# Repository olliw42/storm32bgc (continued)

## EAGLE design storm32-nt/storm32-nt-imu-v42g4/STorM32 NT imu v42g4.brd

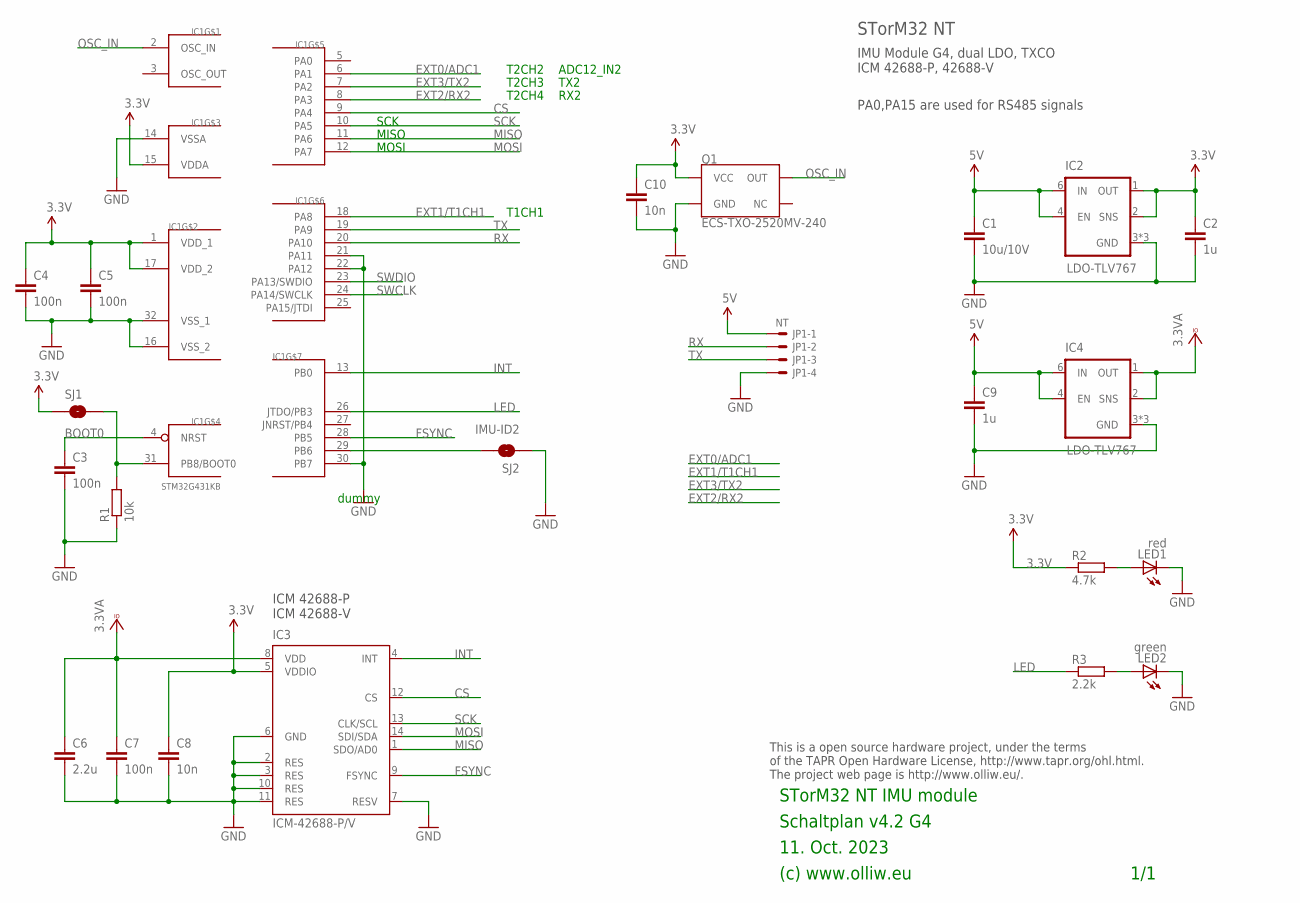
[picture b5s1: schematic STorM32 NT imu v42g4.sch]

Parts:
C1: 10u/10V; C1206
C2: 1u; C0603
C3, C4, C5, C7: 100n; C0402
C6: 2.2u; C0603
C8, C10: 10n; C0402
C9: 1u; C0402
IC1: STM32G431KB; UFQFPN32
IC2, IC4: LDO-TLV767; WSON-6-2X2
IC3: ICM-42688-P/V; LGA14-2.5X3
JP1: NT; SM04B-SRSS-TB
LED1: red; CHIPLED_0603
LED2: green; CHIPLED_0603
Q1: ECS-TXO-2520MV-240; TXCO-25X20
R1: 10k; R0402
R2: 4.7k; R0402
R3: 2.2k; R0402
SJ1: BOOT0; SJ_2S-NO
SJ2: IMU-ID2; SJ_2S-NO

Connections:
3.3V: C2.1, C4.1, C5.1, C8.1, C10.1, IC1.1 (VDD_1), IC1.15 (VDDA), IC1.17 (VDD_2), IC2.1 (OUT), IC2.2 (SNS), IC3.5 (VDDIO), Q1.4 (VCC), R2.1, SJ1.1
3.3VA: C6.1, C7.1, IC3.8 (VDD), IC4.1 (OUT), IC4.2 (SNS)
5V: C1.1, C9.1, IC2.4 (EN), IC2.6 (IN), IC4.4 (EN), IC4.6 (IN), JP1.1
CS: IC1.9 (PA4), IC3.12 (CS)
EXT0/ADC1: IC1.6 (PA1)
EXT1/T1CH1: IC1.18 (PA8)
EXT2/RX2: IC1.8 (PA3)
EXT3/TX2: IC1.7 (PA2)
FSYNC: IC1.28 (PB5), IC3.9 (FSYNC)
GND: C1.2, C2.2, C3.2, C4.2, C5.2, C6.2, C7.2, C8.2, C9.2, C10.2, IC1.14 (VSSA), IC1.16 (VSS_2), IC1.21 (PA11), IC1.22 (PA12), IC1.30 (PB7), IC1.32 (VSS_1), IC2.3 (GND), IC2.5 (GND), IC2.7 (GND), IC3.2 (RES), IC3.3 (RES), IC3.6 (GND), IC3.7 (RESV), IC3.10 (RES), IC3.11 (RES), IC4.3 (GND), IC4.5 (GND), IC4.7 (GND), JP1.4, LED1.C, LED2.C, Q1.2 (GND), R1.1, SJ2.1
INT: IC1.13 (PB0), IC3.4 (INT)
LED: IC1.26 (JTDO/PB3), R3.1
MISO: IC1.11 (PA6), IC3.1 (SDO/AD0)
MOSI: IC1.12 (PA7), IC3.14 (SDI/SDA)
unnamed: C3.1, IC1.4 (NRST)
unnamed: LED2.A, R3.2
unnamed: IC1.31 (PB8/BOOT0), R1.2, SJ1.2
unnamed: IC1.29 (PB6), SJ2.2
unnamed: LED1.A, R2.2
OSC_IN: IC1.2 (OSC_IN), Q1.3 (OUT)
RX: IC1.20 (PA10), JP1.2
SCK: IC1.10 (PA5), IC3.13 (CLK/SCL)
SWCLK: IC1.24 (PA14/SWCLK)
SWDIO: IC1.23 (PA13/SWDIO)
TX: IC1.19 (PA9), JP1.3

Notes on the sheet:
11. Oct. 2023
(c) www.olliw.eu
STorM32 NT IMU module
Schaltplan v4.2 G4
This is a open source hardware project, under the terms of the TAPR Open Hardware License, http://www.tapr.org/ohl.html. The project web page is http://www.olliw.eu/.
1/1
IMU Module G4, dual LDO, TXCO ICM 42688-P, 42688-V
STorM32 NT
SCK
MISO
MOSI
dummy
T2CH3
RX2
TX2
ICM 42688-P ICM 42688-V
T2CH2
ADC12_IN2
T2CH4
T1CH1
PA0,PA15 are used for RS485 signals

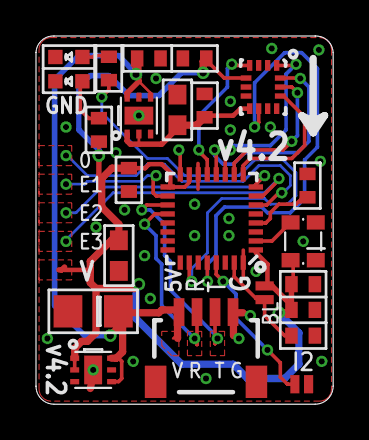
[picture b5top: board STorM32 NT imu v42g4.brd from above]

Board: 2 copper layers, 16.5 x 20.5 mm, 23 parts (0 on the bottom side), 19 nets.

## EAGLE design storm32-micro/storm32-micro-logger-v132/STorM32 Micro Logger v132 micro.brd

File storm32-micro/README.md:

STorM32 Micro Boards
====================

Schemes and designs by OlliW.<br>

The STorM32 Micro boards offered in this folder are published as open source hardware, under the terms of the TAPR Open Hardware License as published by the Free Hardware Foundation, see http://www.tapr.org/ohl.html.

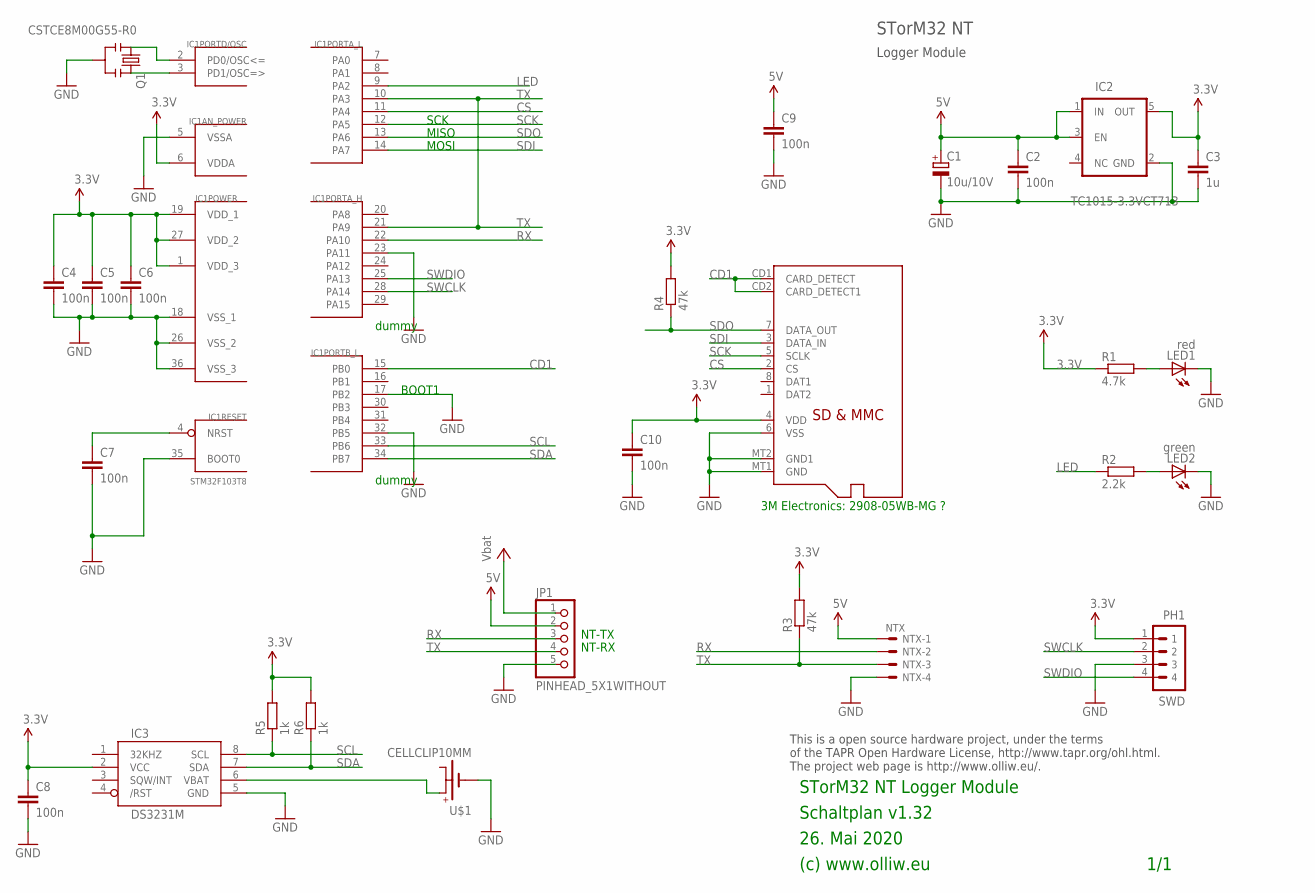
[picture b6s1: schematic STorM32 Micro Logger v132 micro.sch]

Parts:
C1: 10u/10V; SMC_B
C2, C9: 100n; C0603
C3: 1u; C0603
C4, C5, C6, C7, C8, C10: 100n; C0402
IC1: STM32F103T8; VFQFPN36
IC2: TC1015-3.3VCT713; SOT23-5
IC3: DS3231M; SO08
JP1: PINHEAD_5X1WITHOUT; PINHEAD_5X1_WO
LED1: red; CHIPLED_0603
LED2: green; CHIPLED_0603
NTX: NTX; SM04B-SRSS-TB
PH1: SWD; 4X1_1P27_OCT_BILEX
Q1: CSTCE8M00G55-R0; RESONATOR-SMD
R1: 4.7k; R0402
R2: 2.2k; R0402
R3, R4: 47k; R0402
R5, R6: 1k; R0402
U1: 3M 2908-05WB-MG ??; MICROSD
U$1: CELLCLIP10MM; CELLCLIP-10MM

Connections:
3.3V: C3.1, C4.1, C5.1, C6.1, C8.1, C10.1, IC1.1 (VDD_3), IC1.6 (VDDA), IC1.19 (VDD_1), IC1.27 (VDD_2), IC2.5 (OUT), IC3.2 (VCC), PH1.1, R1.1, R3.2, R4.2, R5.2, R6.2, U1.4 (VDD)
5V: C1.+, C2.1, C9.1, IC2.1 (IN), IC2.3 (EN), JP1.2, NTX.1
BAT+: IC3.6 (VBAT), U$1.P$2 (BAT+)
CD1: IC1.15 (PB0), U1.CD1 (CARD_DETECT), U1.CD2 (CARD_DETECT1)
CS: IC1.11 (PA4), U1.2 (CS)
GND: C1.-, C2.2, C3.2, C4.2, C5.2, C6.2, C7.2, C8.2, C9.2, C10.2, IC1.5 (VSSA), IC1.17 (PB2), IC1.18 (VSS_1), IC1.23 (PA11), IC1.26 (VSS_2), IC1.32 (PB5), IC1.35 (BOOT0), IC1.36 (VSS_3), IC2.2 (GND), IC3.5 (GND), JP1.5, LED1.C, LED2.C, NTX.4, PH1.3, Q1.2, U1.6 (VSS), U1.MT1 (GND), U1.MT2 (GND1), U$1.P$1 (GND)
LED: IC1.9 (PA2), R2.1
unnamed: C7.1, IC1.4 (NRST)
unnamed: LED2.A, R2.2
unnamed: IC1.2 (PD0/OSC<=), Q1.1
unnamed: IC1.3 (PD1/OSC=>), Q1.3
unnamed: LED1.A, R1.2
RX: IC1.22 (PA10), JP1.3, NTX.2
SCK: IC1.12 (PA5), U1.5 (SCLK)
SCL: IC1.33 (PB6), IC3.8 (SCL), R5.1
SDA: IC1.34 (PB7), IC3.7 (SDA), R6.1
SDI: IC1.14 (PA7), U1.3 (DATA_IN)
SDO: IC1.13 (PA6), R4.1, U1.7 (DATA_OUT)
SWCLK: IC1.28 (PA14), PH1.2
SWDIO: IC1.25 (PA13), PH1.4
TX: IC1.10 (PA3), IC1.21 (PA9), JP1.4, NTX.3, R3.1
VCC: JP1.1

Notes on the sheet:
26. Mai 2020
(c) www.olliw.eu
STorM32 NT Logger Module
Schaltplan v1.32
This is a open source hardware project, under the terms of the TAPR Open Hardware License, http://www.tapr.org/ohl.html. The project web page is http://www.olliw.eu/.
1/1
Logger Module
STorM32 NT
SCK
MISO
MOSI
BOOT1
dummy
3M Electronics: 2908-05WB-MG ?
NT-RX
NT-TX

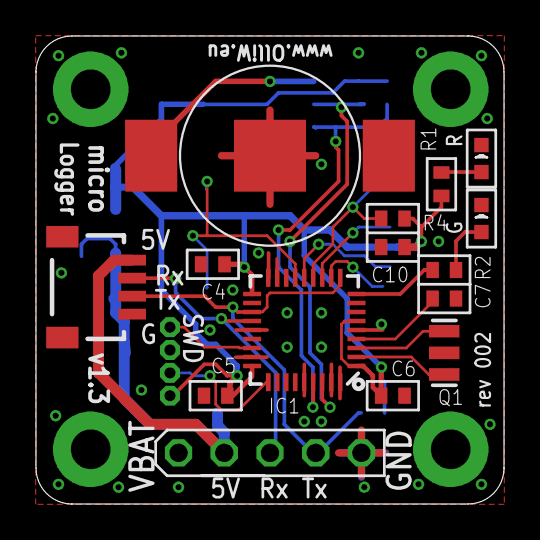
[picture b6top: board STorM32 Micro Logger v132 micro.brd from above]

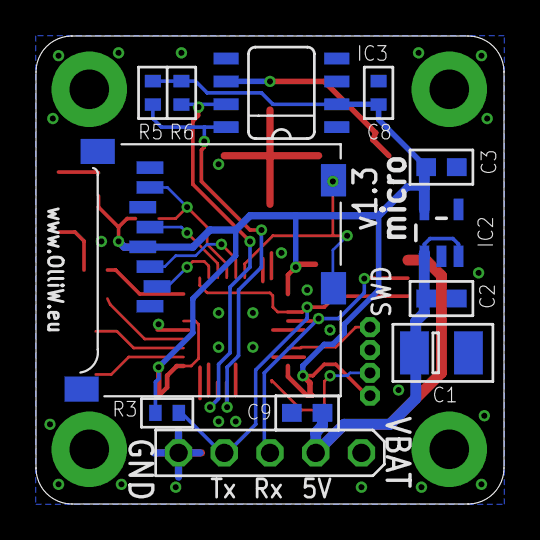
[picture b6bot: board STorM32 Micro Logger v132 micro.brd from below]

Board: 2 copper layers, 26.0 x 26.0 mm, 27 parts (11 on the bottom side), 21 nets.

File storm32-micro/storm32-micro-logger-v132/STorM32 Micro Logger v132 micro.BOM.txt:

Stückliste exportiert aus C:/Users/Olli/Documents/GitHub/storm32bgc/storm32-micro/storm32-micro-logger-v132/STorM32 Micro Logger v132 micro.sch am 05.06.2020 16:31

Part Value              Device                Package            Description                                                 
C1   10u/10V            CPOL-EUSMCB           SMC_B              POLARIZED CAPACITOR, European symbol                        
C2   100n               C-EUC0603             C0603              CAPACITOR, European symbol                                  
C3   1u                 C-EUC0603             C0603              CAPACITOR, European symbol                                  
C4   100n               C-EUC0402             C0402              CAPACITOR, European symbol                                  
C5   100n               C-EUC0402             C0402              CAPACITOR, European symbol                                  
C6   100n               C-EUC0402             C0402              CAPACITOR, European symbol                                  
C7   100n               C-EUC0402             C0402              CAPACITOR, European symbol                                  
C8   100n               C-EUC0402             C0402              CAPACITOR, European symbol                                  
C9   100n               C-EUC0603             C0603              CAPACITOR, European symbol                                  
C10  100n               C-EUC0402             C0402              CAPACITOR, European symbol                                  
IC1  STM32F103T8        STM32F10XTXU6         VFQFPN36           STM32F101/103 36pad VFQPFN36                                
IC2  TC1015-3.3VCT713   V_REG_TPS76433SOT23-5 SOT23-5            Voltage Regulator                                           
IC3  DS3231M            DS3231M               SO08                                                                           
JP1  PINHEAD_5X1WITHOUT PINHEAD_5X1WITHOUT    PINHEAD_5X1_WO                                                                 
LED1 red                LEDCHIPLED_0603       CHIPLED_0603       LED                                                         
LED2 green              LEDCHIPLED_0603       CHIPLED_0603       LED                                                         
NTX  NTX                SM04B-SRSS-TB         SM04B-SRSS-TB      Disconnectable Crimp style connector, 1.0mm pitch4 contacts 
PH1  SWD                P4X1_1P27-OCT_BILEX   4X1_1P27_OCT_BILEX                                                             
Q1   CSTCE8M00G55-R0    RESONATORSMD          RESONATOR-SMD      Resonator                                                   
R1   4.7k               R-EU_R0402            R0402              RESISTOR, European symbol                                   
R2   2.2k               R-EU_R0402            R0402              RESISTOR, European symbol                                   
R3   47k                R-EU_R0402            R0402              RESISTOR, European symbol                                   
R4   47k                R-EU_R0402            R0402              RESISTOR, European symbol                                   
R5   1k                 R-EU_R0402            R0402              RESISTOR, European symbol                                   
R6   1k                 R-EU_R0402            R0402              RESISTOR, European symbol                                   
U$1  CELLCLIP10MM       CELLCLIP10MM          CELLCLIP-10MM                                                                  
U1   3M 2908-05WB-MG ?? MICROSD               MICROSD            Micro-SD / Transflash card holder with SPI pinout

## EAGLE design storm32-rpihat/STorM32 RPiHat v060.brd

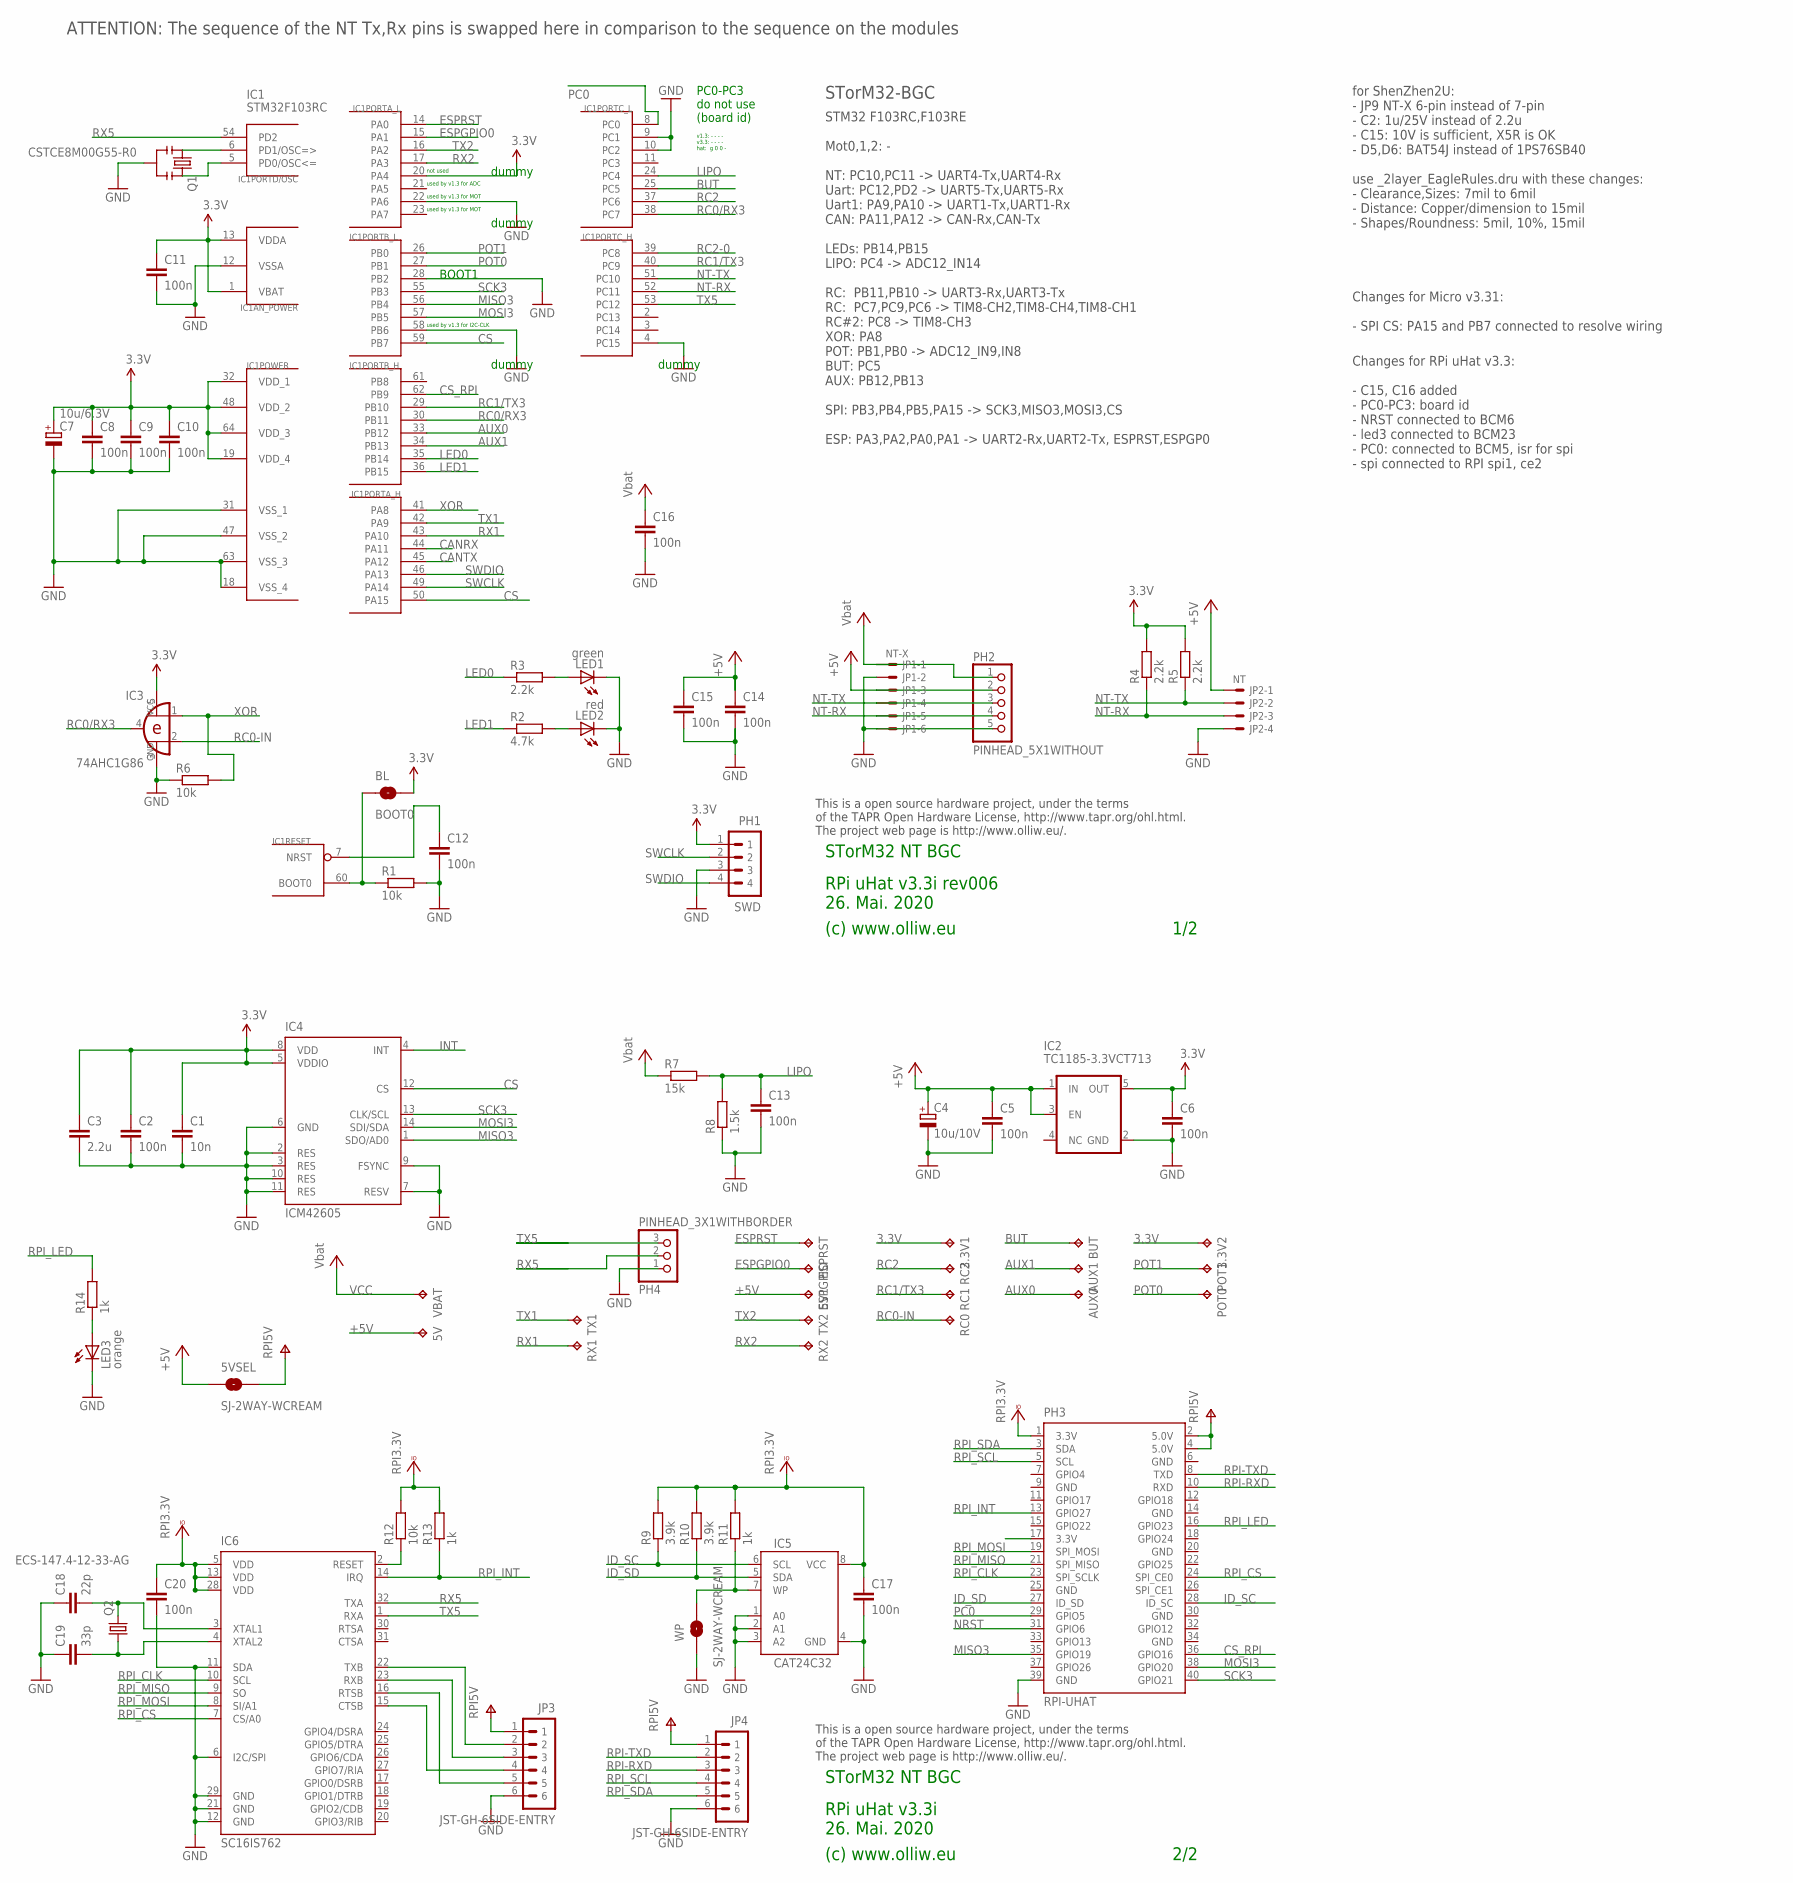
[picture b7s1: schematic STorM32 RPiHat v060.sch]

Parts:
3.3V1, 3.3V2, 5V, 5V1: TPB1,27; B1,27
5VSEL: SJ-2WAY-WCREAM; SJ-2WAY-BIG-WCREAM
AUX0, AUX1: TPB1,27; B1,27
BL: BOOT0; SJ_2S-NO
BUT: TPB1,27; B1,27
C1: 10n; C0402
C2, C6, C8, C9, C10, C11, C12, C13, C14, C15, C17, C20: 100n; C0402
C3: 2.2u; C0603
C4: 10u/10V; SMC_A
C5, C16: 100n; C0603
C7: 10u/6.3V; SMC_A
C18: 22p; C0402
C19: 33p; C0402
ESPGPIO: TPB1,27; B1,27
ESPRST: TPB1,27; B1,27
IC1: STM32F103RCT6; TQFP64
IC2: TC1185-3.3VCT713; SOT23-5
IC3: 74AHC1G86; SOT23-5-VER1
IC4: ICM42605; LGA14-2.5X3
IC5: CAT24C32; TSSOP8-4.3X3
IC6: SC16IS762; QFN-32
JP1: NT-X; SM06B-SRSS-TB
JP2: NT; SM04B-SRSS-TB
JP3, JP4: JST-GH-6SIDE-ENTRY; SM06B-GHS-TB
LED1: green; CHIPLED_0603
LED2: red; CHIPLED_0603
LED3: orange; CHIPLED_0603
PH1: SWD; 4X1_1P27_OCT_BILEX
PH2: PINHEAD_5X1WITHOUT; PINHEAD_5X1_WO
PH3: RPI-UHAT; RPI-40W-UHAT
PH4: PINHEAD_3X1WITHBORDER; PINHEAD_3X1
POT0, POT1: TPB1,27; B1,27
Q1: CSTCE8M00G55-R0; RESONATOR-SMD
Q2: ECS-147.4-12-33-AG; CRYSTAL-SMD-3P2X2P5
R1, R6, R12: 10k; R0402
R2: 4.7k; R0402
R3, R4, R5: 2.2k; R0402
R7: 15k; R0402
R8: 1.5k; R0402
R9, R10: 3.9k; R0402
R11, R13, R14: 1k; R0402
RC0, RC1, RC2: TPB1,27; B1,27
RX1, RX2: TPB1,27; B1,27
TX1, TX2: TPB1,27; B1,27
VBAT: TPB1,27; B1,27
WP: SJ-2WAY-WCREAM; SJ-2WAY-BIG-WCREAM

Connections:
3.3V: 3.3V1.TP, 3.3V2.TP, BL.2, C1.1, C2.1, C3.1, C6.1, C7.+, C8.1, C9.1, C10.1, C11.1, IC1.1 (VBAT), IC1.13 (VDDA), IC1.19 (VDD_4), IC1.20 (PA4), IC1.32 (VDD_1), IC1.48 (VDD_2), IC1.64 (VDD_3), IC2.5 (OUT), IC3.5 (VCC), IC4.5 (VDDIO), IC4.8 (VDD), PH1.1, R4.2, R5.2
+5V: 5V.TP, 5V1.TP, 5VSEL.1, C4.+, C5.1, C14.1, C15.1, IC2.1 (IN), IC2.3 (EN), JP1.3, JP2.1, PH2.2
AUX0: AUX0.TP, IC1.33 (PB12)
AUX1: AUX1.TP, IC1.34 (PB13)
BOOT0: BL.1, IC1.60 (BOOT0), R1.1
BUT: BUT.TP, IC1.25 (PC5)
CANRX: IC1.44 (PA11)
CANTX: IC1.45 (PA12)
CS: IC1.50 (PA15), IC1.59 (PB7), IC4.12 (CS)
CS_RPI: IC1.62 (PB9), PH3.36 (GPIO16)
CTSB: IC6.15 (CTSB), JP3.4
ESPGPIO0: ESPGPIO.TP, IC1.15 (PA1)
ESPRST: ESPRST.TP, IC1.14 (PA0)
GND: C1.2, C2.2, C3.2, C4.-, C5.2, C6.2, C7.-, C8.2, C9.2, C10.2, C11.2, C12.2, C13.2, C14.2, C15.2, C16.2, C17.2, C18.1, C19.1, C20.2, IC1.4 (PC15), IC1.9 (PC1), IC1.10 (PC2), IC1.12 (VSSA), IC1.18 (VSS_4), IC1.22 (PA6), IC1.28 (PB2), IC1.31 (VSS_1), IC1.47 (VSS_2), IC1.58 (PB6), IC1.63 (VSS_3), IC2.2 (GND), IC3.3 (GND), IC4.2 (RES), IC4.3 (RES), IC4.6 (GND), IC4.7 (RESV), IC4.9 (FSYNC), IC4.10 (RES), IC4.11 (RES), IC5.1 (A0), IC5.2 (A1), IC5.3 (A2), IC5.4 (GND), IC6.6 (I2C/SPI), IC6.11 (SDA), IC6.12 (GND), IC6.21 (GND), IC6.29 (GND), JP1.2, JP1.6, JP2.4, JP3.6, JP4.6, LED1.C, LED2.C, LED3.C, PH1.3, PH2.5, PH3.6 (GND), PH3.9 (GND), PH3.14 (GND), PH3.20 (GND), PH3.25 (GND), PH3.30 (GND), PH3.34 (GND), PH3.39 (GND), PH4.1, Q1.2, R1.2, R6.1, R8.1, WP.1
ID_SC: IC5.6 (SCL), PH3.28 (ID_SC), R9.1
ID_SD: IC5.5 (SDA), PH3.27 (ID_SD), R10.1
INT: IC4.4 (INT)
LED0: IC1.35 (PB14), R3.1
LED1: IC1.36 (PB15), R2.1
LIPO: C13.1, IC1.24 (PC4), R7.2, R8.2
MISO3: IC1.56 (PB4), IC4.1 (SDO/AD0), PH3.35 (GPIO19)
MOSI3: IC1.57 (PB5), IC4.14 (SDI/SDA), PH3.38 (GPIO20)
unnamed: IC6.2 (RESET), R12.1
unnamed: C18.2, IC6.3 (XTAL1), Q2.3 (2)
unnamed: C19.2, IC6.4 (XTAL2), Q2.1
unnamed: LED1.A, R3.2
unnamed: LED2.A, R2.2
unnamed: LED3.A, R14.1
unnamed: IC1.5 (PD0/OSC<=), Q1.3
unnamed: IC1.6 (PD1/OSC=>), Q1.1
unnamed: IC5.7 (WP), R11.1, WP.2
NRST: C12.1, IC1.7 (NRST), PH3.31 (GPIO6)
NT-RX: IC1.52 (PC11), JP1.5, JP2.3, PH2.4, R4.1
NT-TX: IC1.51 (PC10), JP1.4, JP2.2, PH2.3, R5.1
PC0: IC1.8 (PC0), PH3.29 (GPIO5)
POT0: IC1.27 (PB1), POT0.TP
POT1: IC1.26 (PB0), POT1.TP
RC0-IN: IC3.2 (I1), RC0.TP
RC0/RX3: IC1.30 (PB11), IC1.38 (PC7), IC3.4 (O)
RC1/TX3: IC1.29 (PB10), IC1.40 (PC9), RC1.TP
RC2: IC1.37 (PC6), RC2.TP
RC2-0: IC1.39 (PC8)
RPI3.3V: C17.1, C20.1, IC5.8 (VCC), IC6.5 (VDD), IC6.13 (VDD), IC6.28 (VDD), PH3.1 (3.3V), R9.2, R10.2, R11.2, R12.2, R13.2
RPI5V: 5VSEL.2, JP3.1, JP4.1, PH3.2 (5.0V), PH3.4 (5.0V)
RPI-RXD: JP4.3, PH3.10 (RXD)
RPI-TXD: JP4.2, PH3.8 (TXD)
RPI_CLK: IC6.10 (SCL), PH3.23 (SPI_SCLK)
RPI_CS: IC6.7 (CS/A0), PH3.24 (SPI_CE0)
RPI_INT: IC6.14 (IRQ), PH3.13 (GPIO27), R13.1
RPI_LED: PH3.16 (GPIO23), R14.2
RPI_MISO: IC6.9 (SO), PH3.21 (SPI_MISO)
RPI_MOSI: IC6.8 (SI/A1), PH3.19 (SPI_MOSI)
RPI_SCL: JP4.4, PH3.5 (SCL)
RPI_SDA: JP4.5, PH3.3 (SDA)
RTSB: IC6.16 (RTSB), JP3.5
RX1: IC1.43 (PA10), RX1.TP
RX2: IC1.17 (PA3), RX2.TP
RX5: IC1.54 (PD2), IC6.32 (TXA), PH4.2 (3)
RXB: IC6.23 (RXB), JP3.3
SCK3: IC1.55 (PB3), IC4.13 (CLK/SCL), PH3.40 (GPIO21)
SWCLK: IC1.49 (PA14), PH1.2
SWDIO: IC1.46 (PA13), PH1.4
TX1: IC1.42 (PA9), TX1.TP
TX2: IC1.16 (PA2), TX2.TP
TX5: IC1.53 (PC12), IC6.1 (RXA), PH4.3 (5)
TXB: IC6.22 (TXB), JP3.2
VCC: C16.1, JP1.1, PH2.1, R7.1, VBAT.TP
XOR: IC1.41 (PA8), IC3.1 (I0), R6.2

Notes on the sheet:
(c) www.olliw.eu
STorM32 NT BGC
This is a open source hardware project, under the terms of the TAPR Open Hardware License, http://www.tapr.org/ohl.html. The project web page is http://www.olliw.eu/.
STM32 F103RC,F103RE Mot0,1,2: - NT: PC10,PC11 -> UART4-Tx,UART4-Rx Uart: PC12,PD2 -> UART5-Tx,UART5-Rx Uart1: PA9,PA10 -> UART1-Tx,UART1-Rx CAN: PA11,PA12 -> CAN-Rx,CAN-Tx LEDs: PB14,PB15 LIPO: PC4 -> ADC12_IN14 RC: PB11,PB10 -> UART3-Rx,UART3-Tx RC: PC7,PC9,PC6 -> TIM8-CH2,TIM8-CH4,TIM8-CH1 RC#2: 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
RPi uHat v3.3i 26. Mai. 2020
STM32F103RC
STorM32-BGC
1/2
2/2
IC1
ATTENTION: The sequence of the NT Tx,Rx pins is swapped here in comparison to the sequence on the modules
BOOT1
dummy
RPi uHat v3.3i rev006 26. Mai. 2020
PC0-PC3 do not use (board id)
for ShenZhen2U: - JP9 NT-X 6-pin instead of 7-pin - C2: 1u/25V instead of 2.2u - C15: 10V is sufficient, X5R is OK - D5,D6: BAT54J instead of 1PS76SB40 use _2layer_EagleRules.dru with these changes: - Clearance,Sizes: 7mil to 6mil - Distance: Copper/dimension to 15mil - Shapes/Roundness: 5mil, 10%,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
Changes for Micro v3.31: - SPI CS: PA15 and PB7 connected to resolve wiring
used by v1.3 for ADC
used by v1.3 for MOT
not used
used by v1.3 for I2C-CLK
v1.3: - - - - v3.3: - - - - hat: g 0 0 -
Changes for RPi uHat v3.3: - C15, C16 added - PC0-PC3: board id - NRST connected to BCM6 - led3 connected to BCM23 - PC0: connected to BCM5, isr for spi - spi connected to RPI spi1, ce2

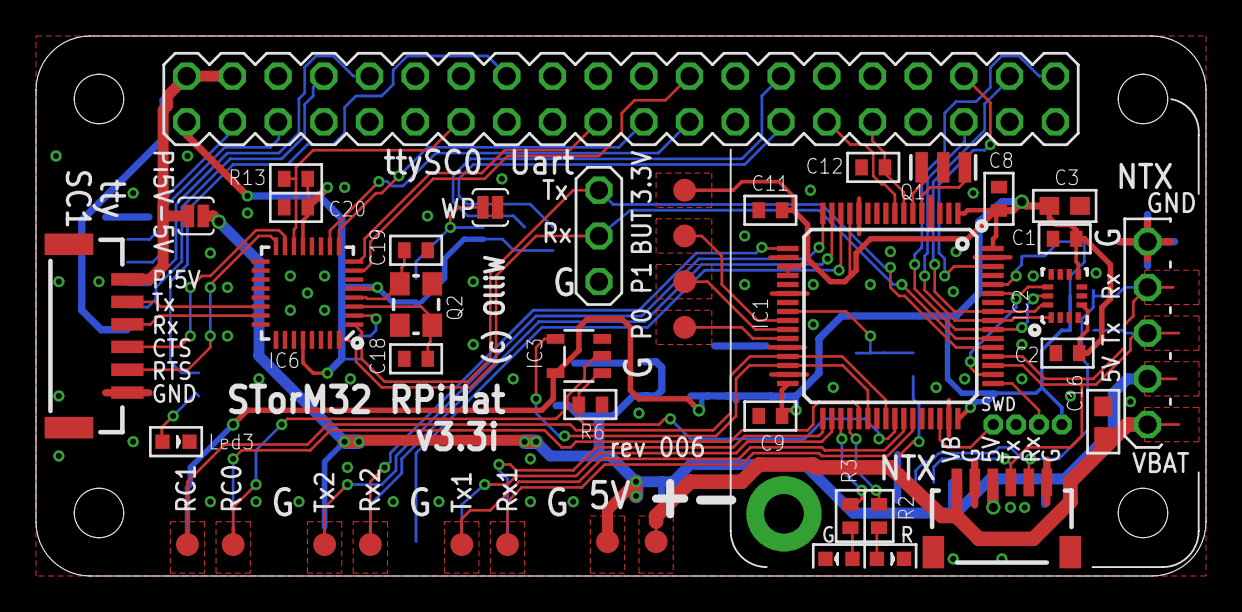
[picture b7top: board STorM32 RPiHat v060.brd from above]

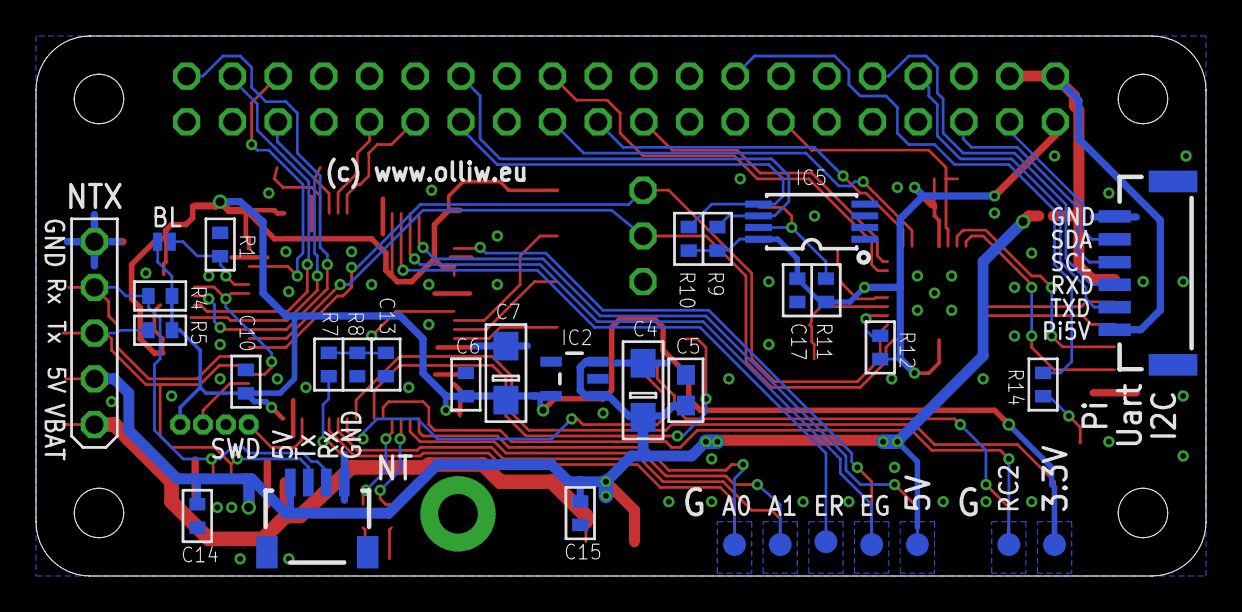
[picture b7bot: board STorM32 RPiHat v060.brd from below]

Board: 2 copper layers, 65.0 x 30.0 mm, 75 parts (31 on the bottom side), 64 nets.

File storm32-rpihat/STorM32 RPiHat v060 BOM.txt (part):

Stückliste exportiert aus C:/Users/Olli/Documents/GitHub/storm32bgc/storm32-rpihat/STorM32 RPiHat v060.sch am 28.05.2020 11:55

Part    Value                 Device                Package             Description                                                 TP_SIGNAL_NAME
3.3V1   TPB1,27               TPB1,27               B1,27               Test pad                                                                  
3.3V2   TPB1,27               TPB1,27               B1,27               Test pad                                                                  
5V      TPB1,27               TPB1,27               B1,27               Test pad                                                                  
5V1     TPB1,27               TPB1,27               B1,27               Test pad                                                                  
5VSEL   SJ-2WAY-WCREAM        SJ-2WAY-WCREAM        SJ-2WAY-BIG-WCREAM                                                                            
AUX0    TPB1,27               TPB1,27               B1,27               Test pad                                                                  
AUX1    TPB1,27               TPB1,27               B1,27               Test pad                                                                  
BL      BOOT0                 SOLDERJUMPERNO        SJ_2S-NO            Solder Jumper                                                             
BUT     TPB1,27               TPB1,27               B1,27               Test pad                                                                  
C1      10n                   C-EUC0402             C0402               CAPACITOR, European symbol                                                
C2      100n                  C-EUC0402             C0402               CAPACITOR, European symbol                                                
C3      2.2u                  C-EUC0603             C0603               CAPACITOR, European symbol                                                
C4      10u/10V               CPOL-EUSMCA           SMC_A               POLARIZED CAPACITOR, European symbol                                      
C5      100n                  C-EUC0603             C0603               CAPACITOR, European symbol                                                
C6      100n                  C-EUC0402             C0402               CAPACITOR, European symbol                                                
C7      10u/6.3V              CPOL-EUSMCA           SMC_A               POLARIZED CAPACITOR, European symbol                                      
C8      100n                  C-EUC0402             C0402               CAPACITOR, European symbol                                                
C9      100n                  C-EUC0402             C0402               CAPACITOR, European symbol                                                
C10     100n                  C-EUC0402             C0402               CAPACITOR, European symbol                                                
C11     100n                  C-EUC0402             C0402               CAPACITOR, European symbol                                                
C12     100n                  C-EUC0402             C0402               CAPACITOR, European symbol                                                
C13     100n                  C-EUC0402             C0402               CAPACITOR, European symbol                                                
C14     100n                  C-EUC0402             C0402               CAPACITOR, European symbol                                                
C15     100n                  C-EUC0402             C0402               CAPACITOR, European symbol                                                
C16     100n                  C-EUC0603             C0603               CAPACITOR, European symbol                                                
C17     100n                  C-EUC0402             C0402               CAPACITOR, European symbol                                                
C18     22p                   C-EUC0402             C0402               CAPACITOR, European symbol                                                
C19     33p                   C-EUC0402             C0402               CAPACITOR, European symbol                                                
C20     100n                  C-EUC0402             C0402               CAPACITOR, European symbol                                                
ESPGPIO TPB1,27               TPB1,27               B1,27               Test pad                                                                  
ESPRST  TPB1,27               TPB1,27               B1,27               Test pad                                                                  
IC1     STM32F103RCT6         STM32F10XRXT6         TQFP64              STM32F101/103 64pin LQFP                                                  
IC2     TC1185-3.3VCT713      V_REG_TPS76433SOT23-5 SOT23-5             Voltage Regulator                                                         
IC3     74AHC1G86             74AHC1G86             SOT23-5-VER1                                                                                  
IC4     ICM42605              ICM42605              LGA14-2.5X3                                                                                   
IC5     CAT24C32              CAT24C32              TSSOP8-4.3X3                                                                                  
IC6     SC16IS762             SC16IS762             QFN-32                                                                                        
JP1     NT-X                  SM06B-SRSS-TB         SM06B-SRSS-TB       Disconnectable Crimp style connector, 1.0mm pitch6 contacts               
JP2     NT                    SM04B-SRSS-TB         SM04B-SRSS-TB       Disconnectable Crimp style connector, 1.0mm pitch4 contacts               
JP3     JST-GH-6SIDE-ENTRY    JST-GH-6SIDE-ENTRY    SM06B-GHS-TB                                                                                  
JP4     JST-GH-6SIDE-ENTRY    JST-GH-6SIDE-ENTRY    SM06B-GHS-TB                                                                                  
LED1    green                 LEDCHIPLED_0603       CHIPLED_0603        LED                                                                       
LED2    red                   LEDCHIPLED_0603       CHIPLED_0603        LED                                                                       
LED3    orange                LEDCHIPLED_0603       CHIPLED_0603        LED                                                                       
PH1     SWD                   P4X1_1P27-OCT_BILEX   4X1_1P27_OCT_BILEX                                                                            
PH2     PINHEAD_5X1WITHOUT    PINHEAD_5X1WITHOUT    PINHEAD_5X1_WO                                                                                
PH3     RPI-UHAT              RPI-UHAT              RPI-40W-UHAT                                                                                  
PH4     PINHEAD_3X1WITHBORDER PINHEAD_3X1WITHBORDER PINHEAD_3X1                                                                                   
POT0    TPB1,27               TPB1,27               B1,27               Test pad                                                                  
POT1    TPB1,27               TPB1,27               B1,27               Test pad                                                                  
Q1      CSTCE8M00G55-R0       RESONATORSMD          RESONATOR-SMD       Resonator                                                                 
Q2      ECS-147.4-12-33-AG    QUARZ3.2X2.5          CRYSTAL-SMD-3P2X2P5                                                                           
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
